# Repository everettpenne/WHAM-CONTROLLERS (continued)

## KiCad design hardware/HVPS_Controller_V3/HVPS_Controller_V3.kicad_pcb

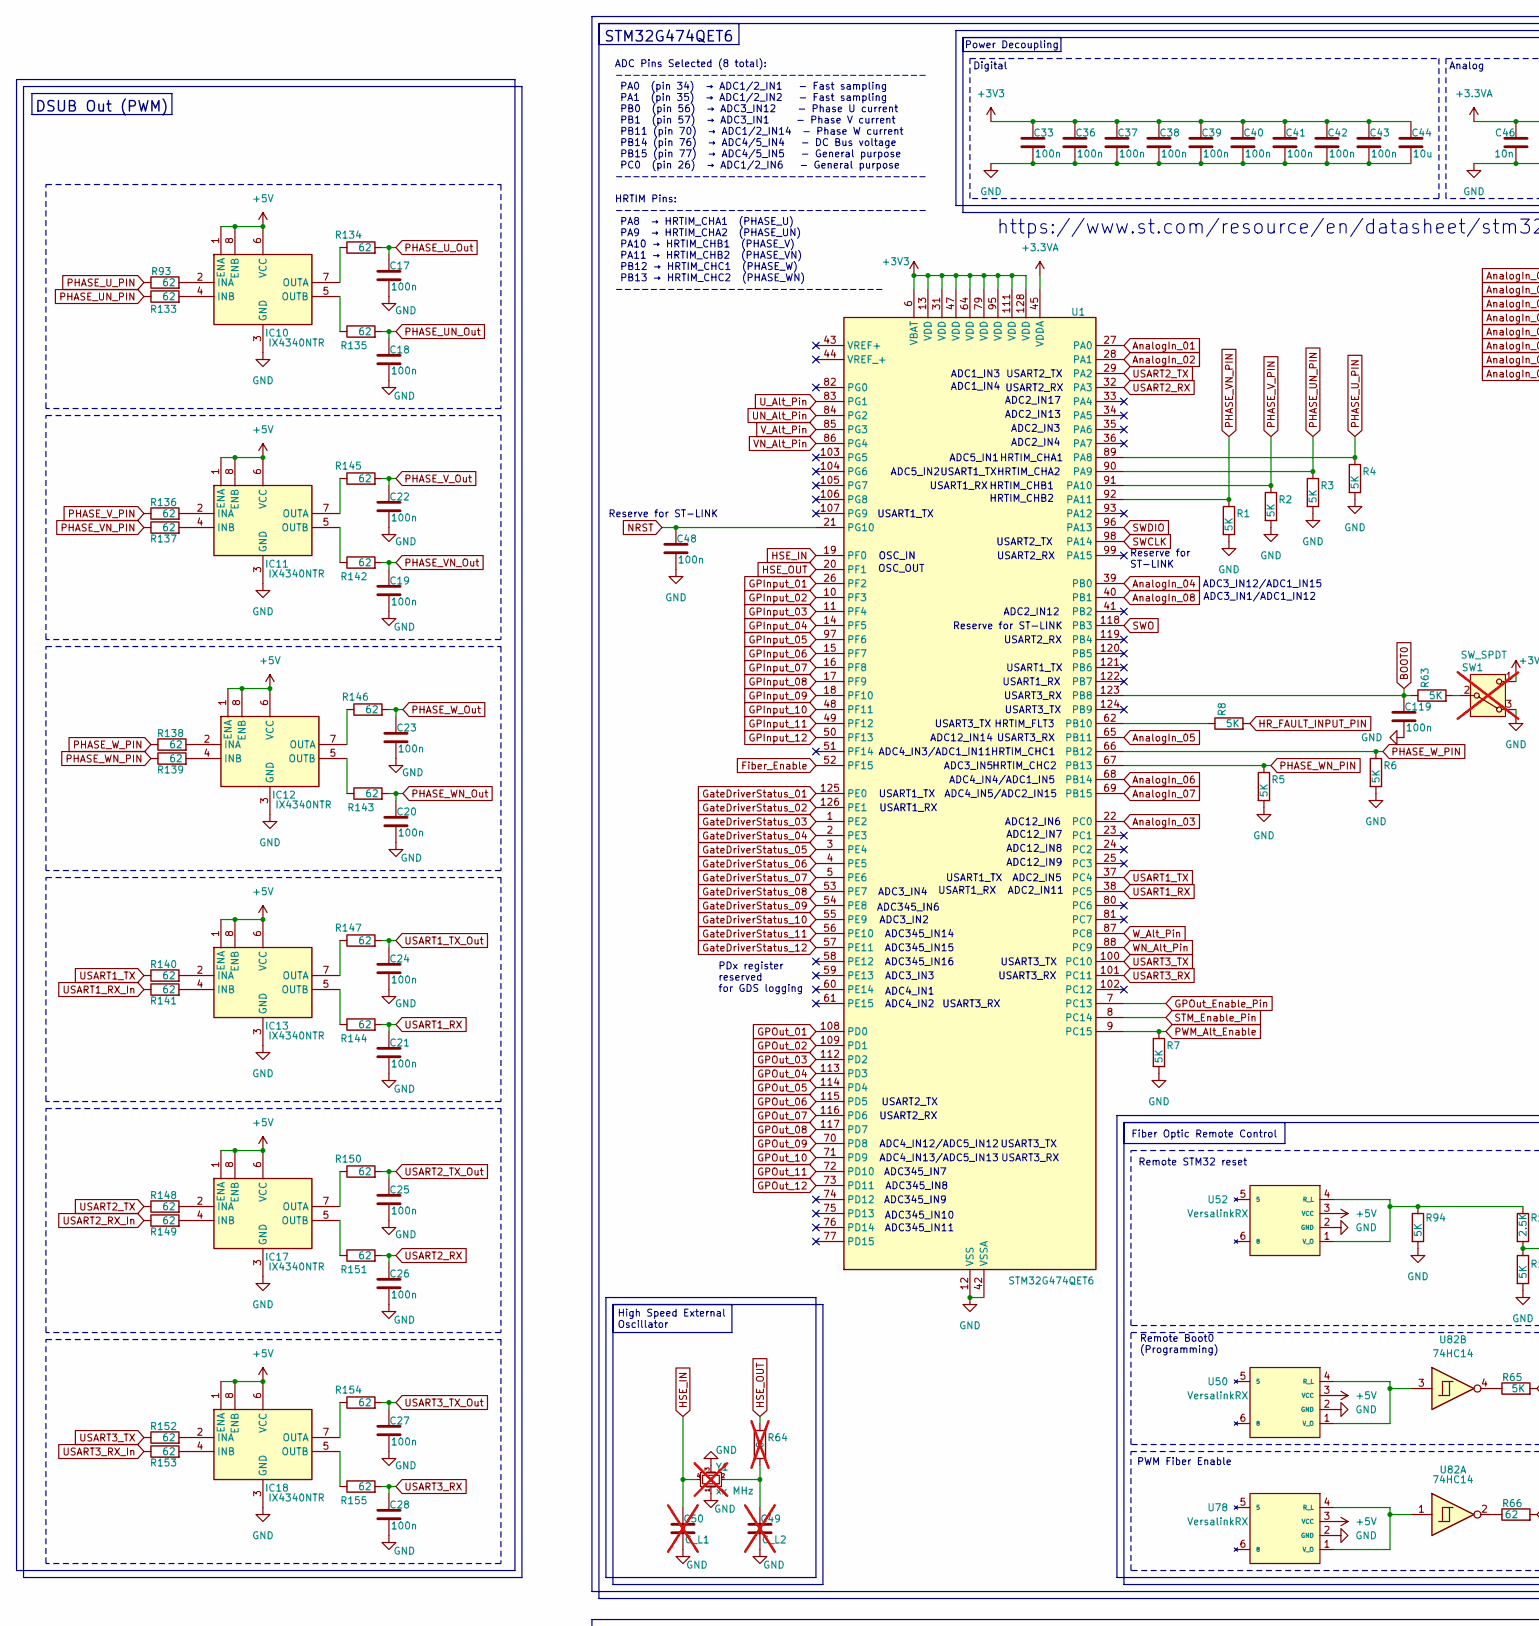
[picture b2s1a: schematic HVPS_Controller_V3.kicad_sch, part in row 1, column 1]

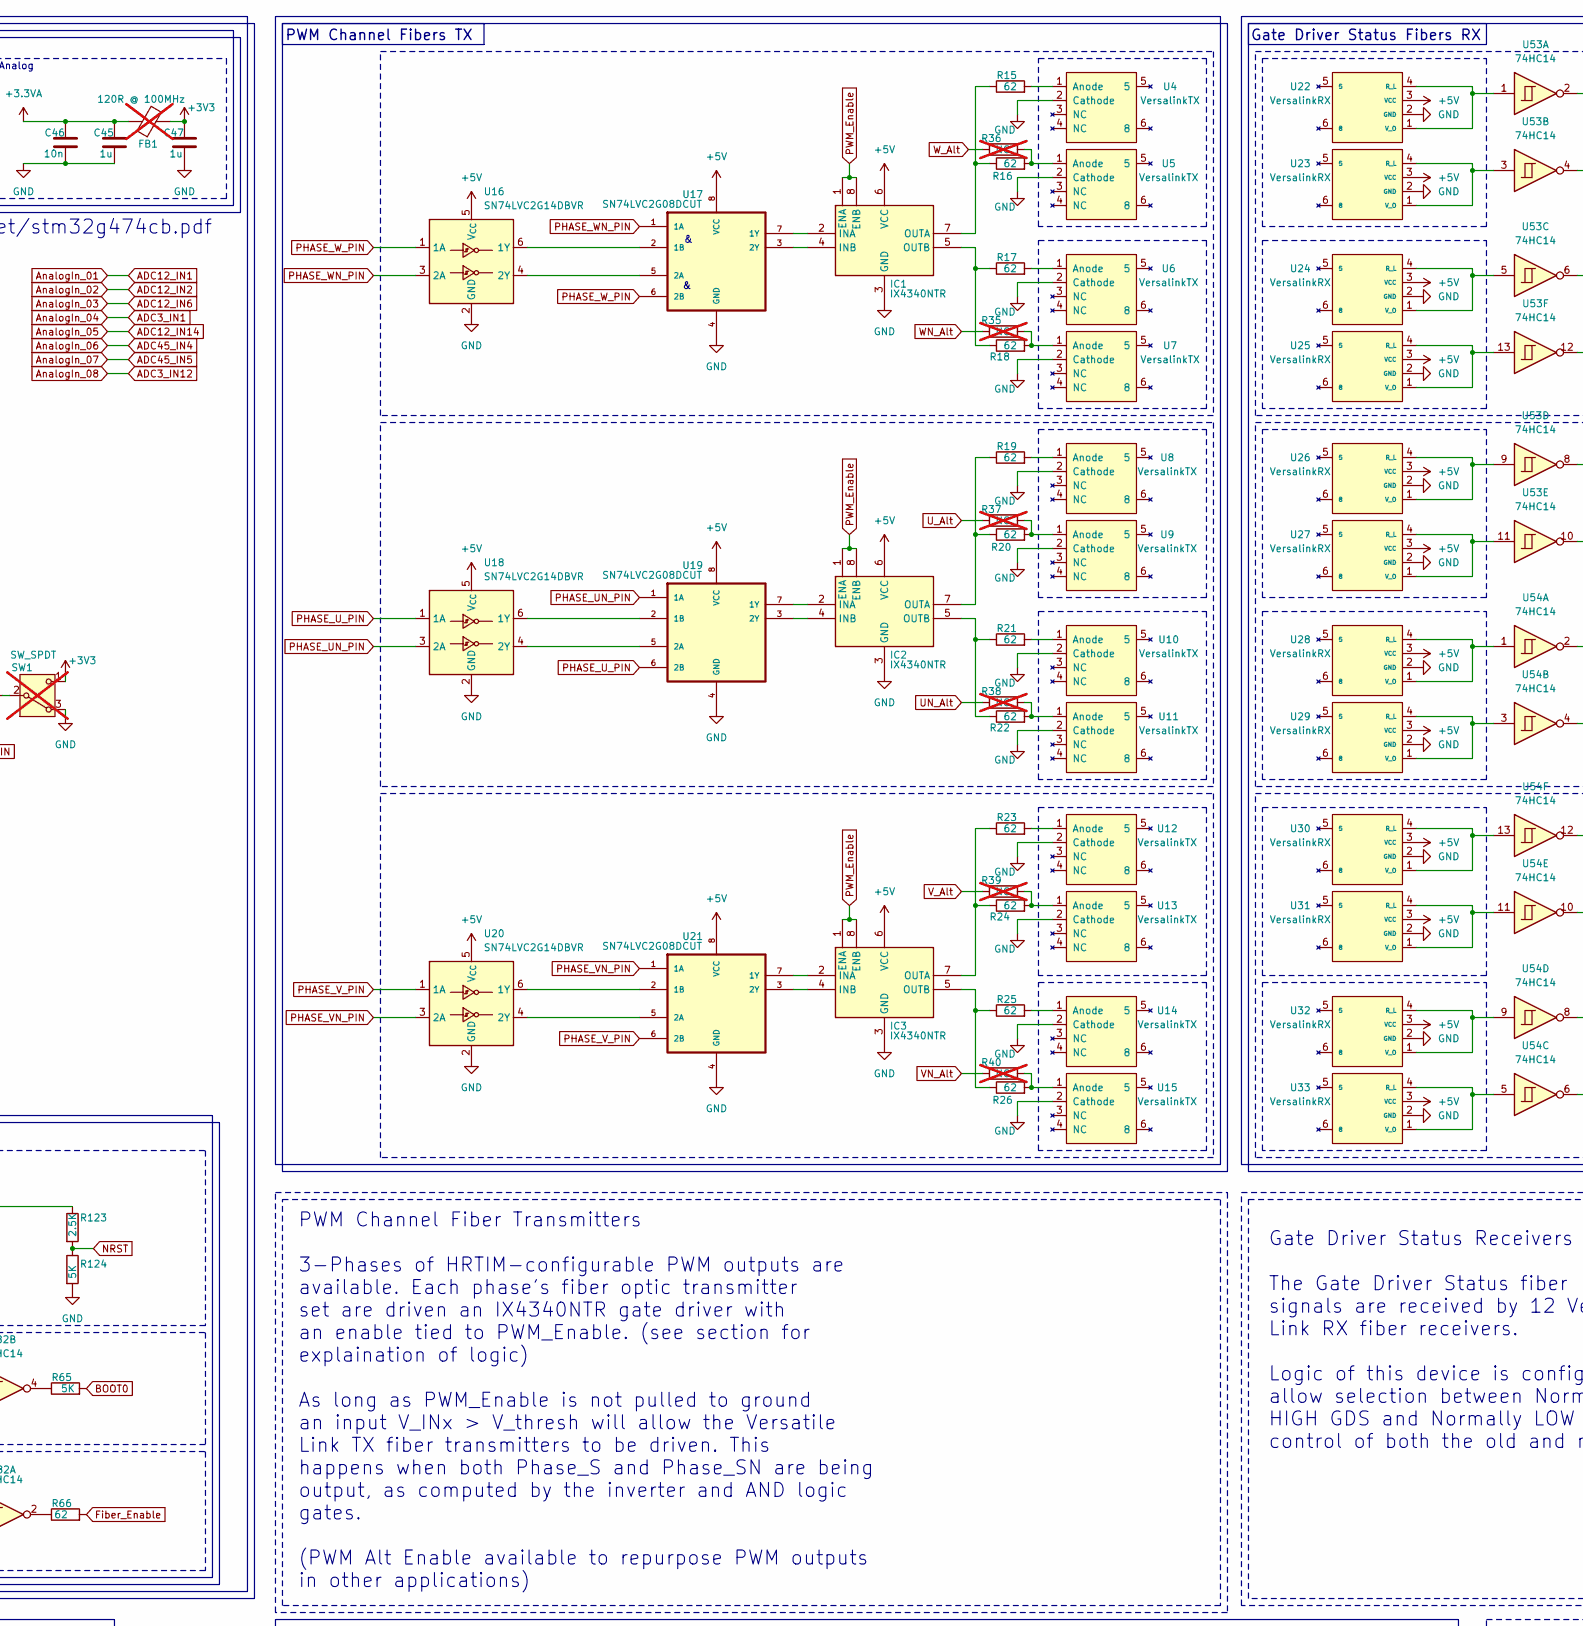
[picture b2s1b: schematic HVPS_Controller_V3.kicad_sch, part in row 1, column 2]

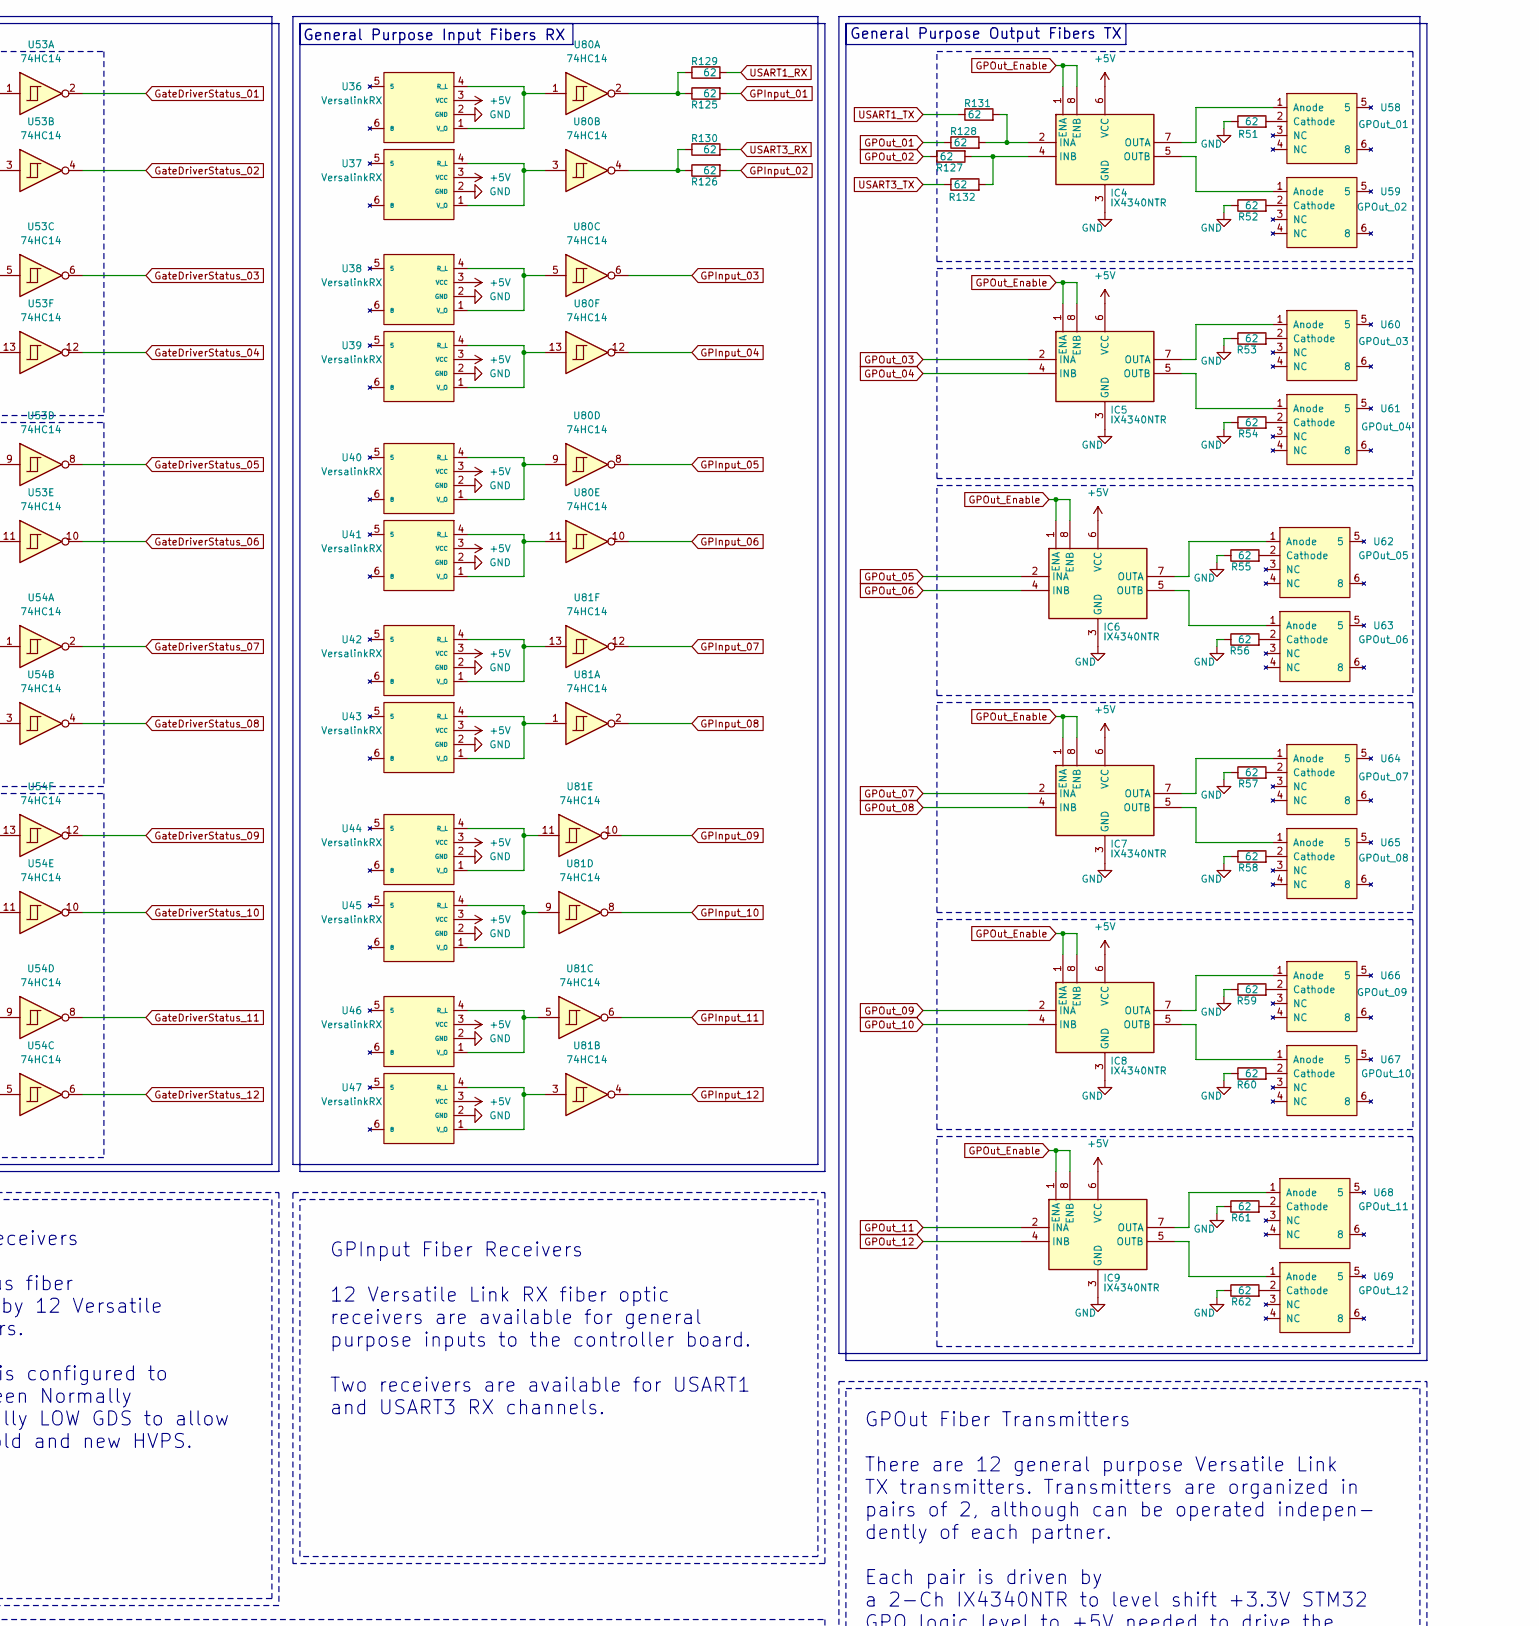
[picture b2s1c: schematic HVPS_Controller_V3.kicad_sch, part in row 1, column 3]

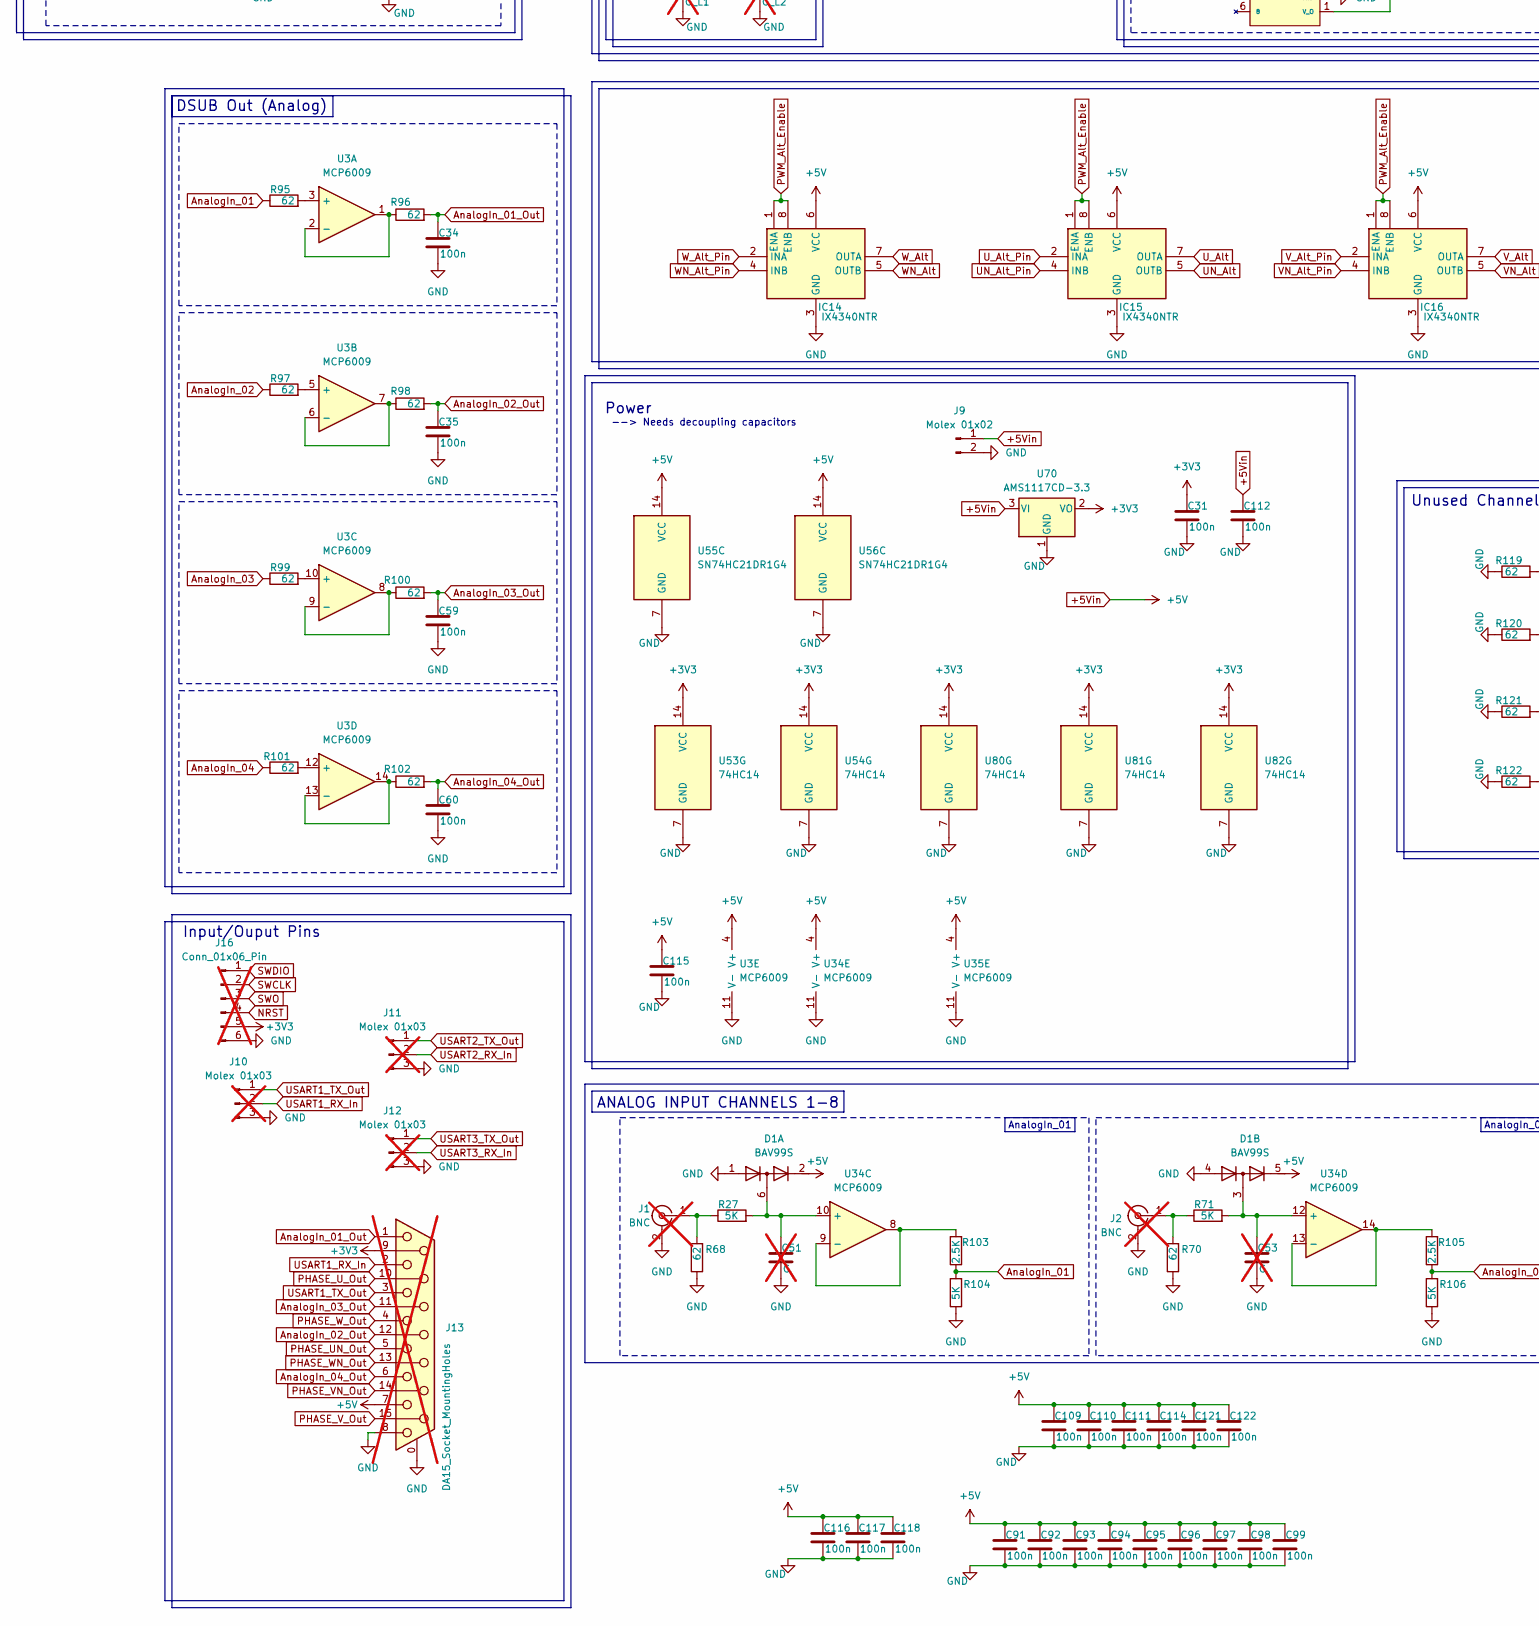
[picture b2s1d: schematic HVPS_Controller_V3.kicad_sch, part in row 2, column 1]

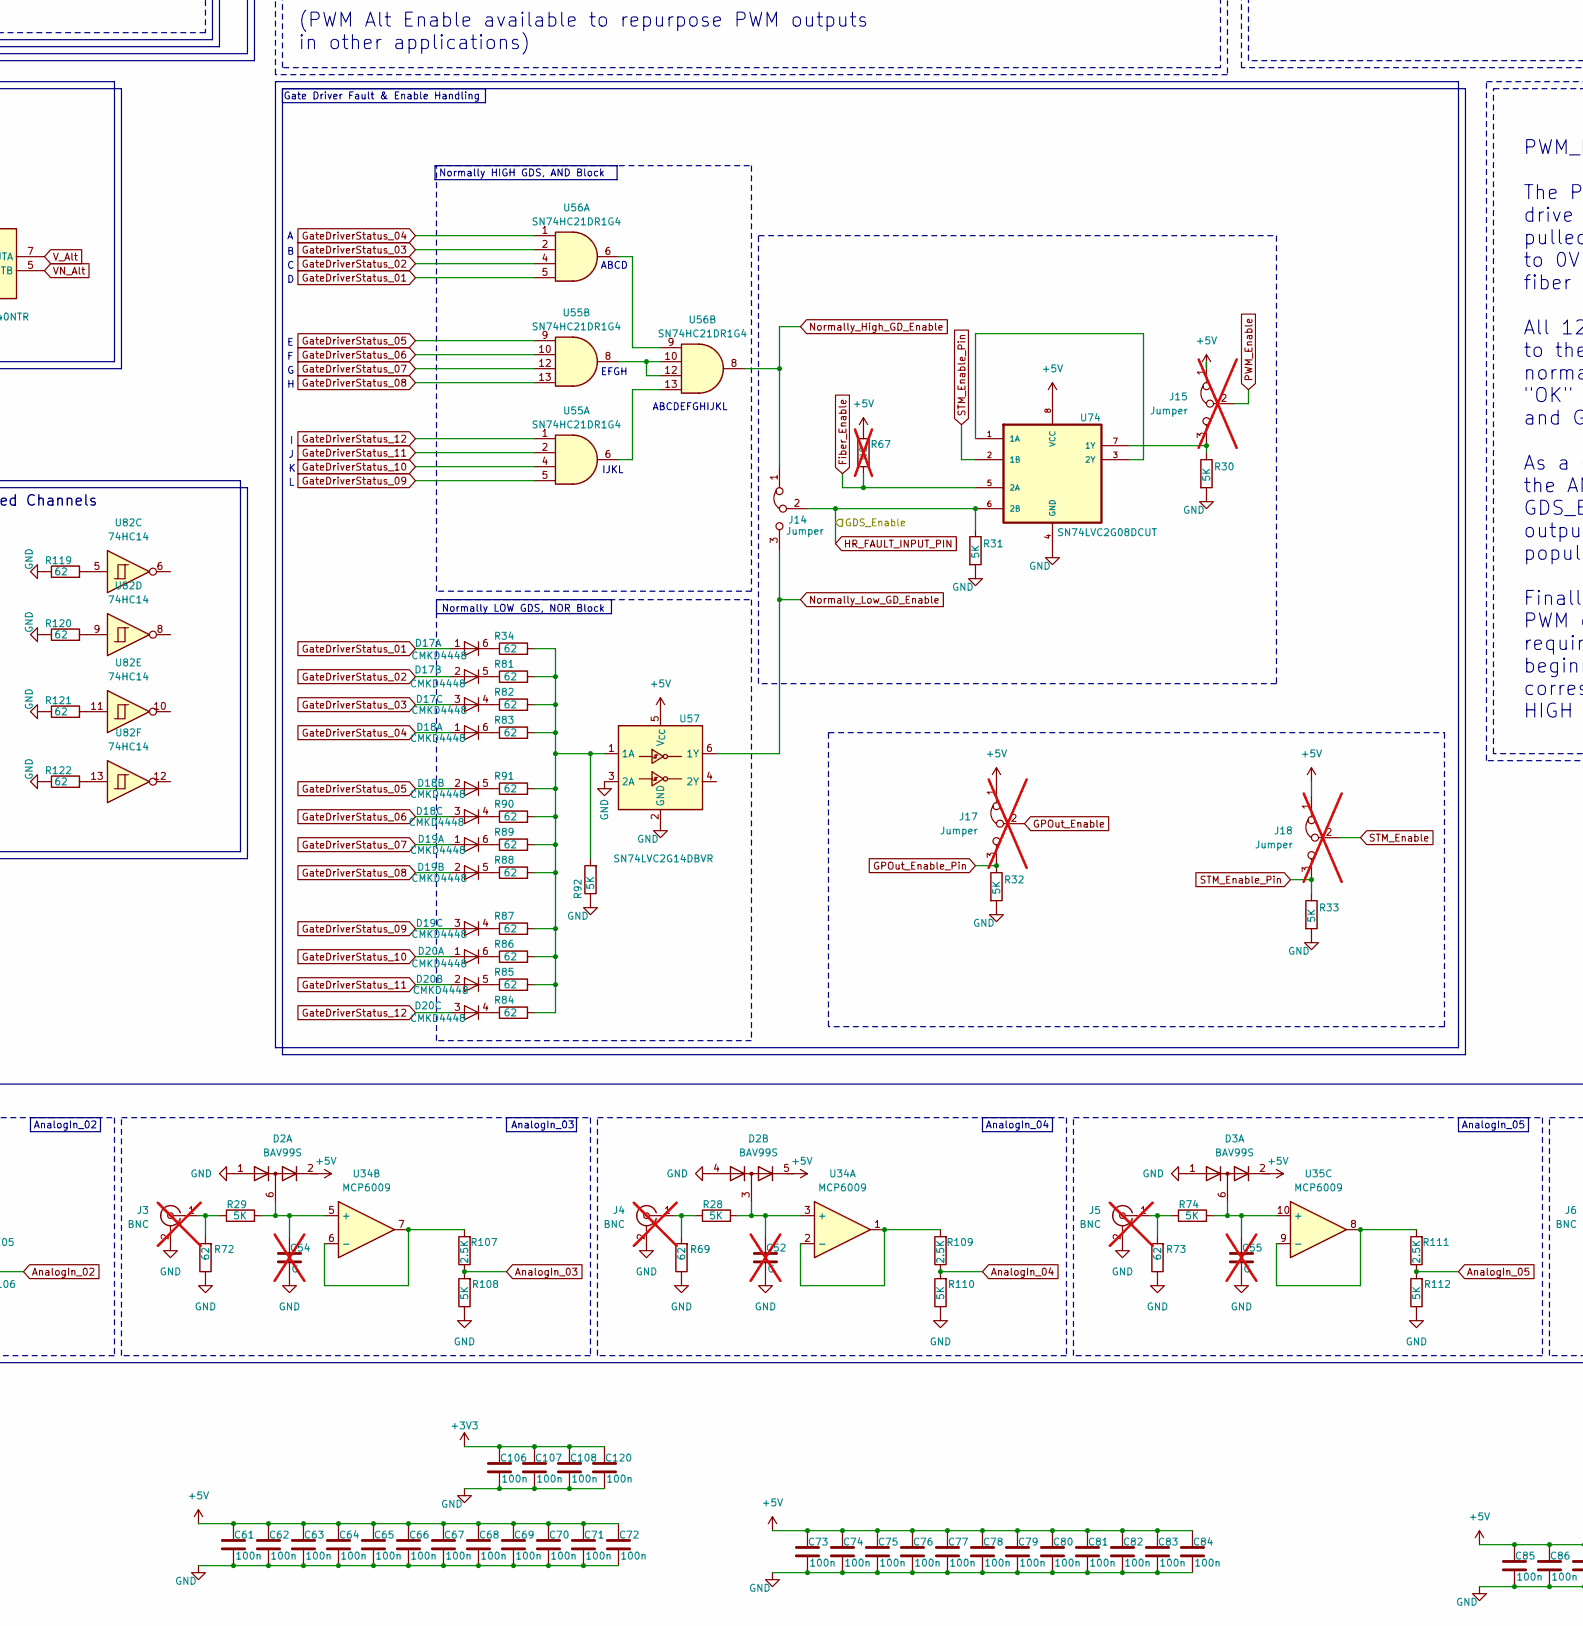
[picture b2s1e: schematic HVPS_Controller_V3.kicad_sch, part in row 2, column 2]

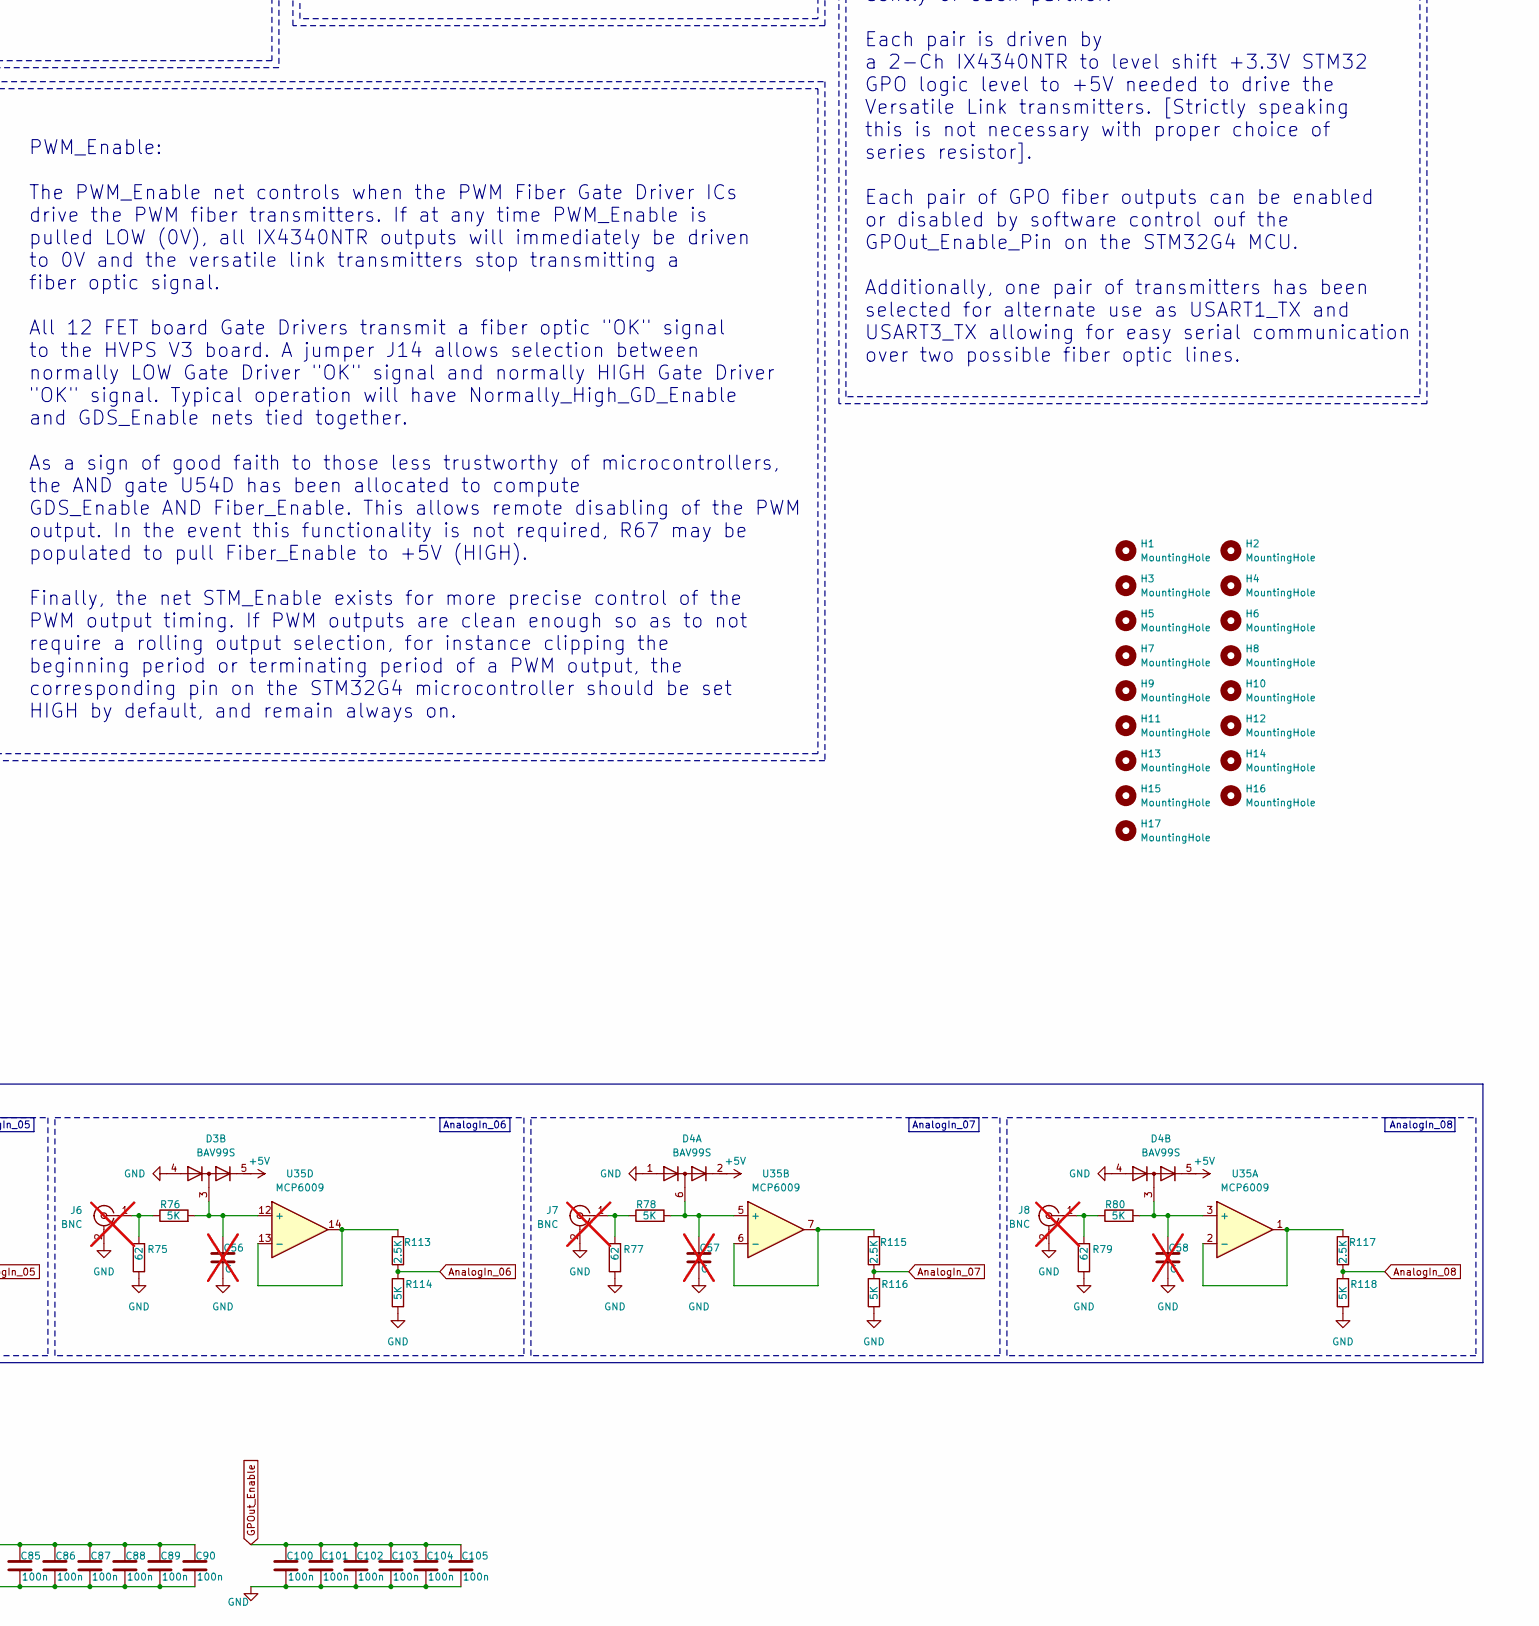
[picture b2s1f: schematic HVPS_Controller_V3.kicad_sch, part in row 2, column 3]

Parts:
C17, C18, C19, C20, C21, C22, C23, C24, C25, C26, C27, C28, C34, C35, C59, C60, C109, C110, C111, C114, C121, C122: 100n; C_1206_3216Metric_Pad1.33x1.80mm_HandSolder
C31, C33, C36, C37, C38, C39, C40, C41, C42, C43, C48, C61, C62, C63, C64, C65, C66, C67, C68, C69, C70, C71, C72, C73, C74, C75, C76, C77, C78, C79, C80, C81, C82, C83, C84, C85, C86, C87, C88, C89, C90, C91, C92, C93, C94, C95, C96, C97, C98, C99, C100, C101, C102, C103, C104, C105, C106, C107, C108, C112, C115, C116, C117, C118, C119, C120: 100n; C_0805_2012Metric_Pad1.18x1.45mm_HandSolder
C44: 10u; C_0805_2012Metric_Pad1.18x1.45mm_HandSolder
C45, C47: 1u; C_0805_2012Metric_Pad1.18x1.45mm_HandSolder
C46: 10n; C_0805_2012Metric_Pad1.18x1.45mm_HandSolder
C49: C_L2; C_0805_2012Metric_Pad1.18x1.45mm_HandSolder; not fitted
C50: C_L1; C_0805_2012Metric_Pad1.18x1.45mm_HandSolder; not fitted
C51, C52, C53, C54, C55, C56, C57, C58: C; C_1206_3216Metric_Pad1.33x1.80mm_HandSolder; not fitted
D1, D2, D3, D4: BAV99S; SOT-363_SC-70-6
D17, D18, D19, D20: CMKD4448; SOT-363_SC-70-6
FB1: 120R @ 100MHz; Ferrite_1206_3216Metric_Pad1.42x1.75mm_BigPads; not fitted
H1, H2, H3, H4, H5, H6, H7, H8, H9, H10, H11, H12, H13, H14, H15, H16, H17: MountingHole; MountingHole_2mm
IC1, IC2, IC3, IC4, IC5, IC6, IC7, IC8, IC9, IC10, IC11, IC12, IC13, IC14, IC15, IC16, IC17, IC18: IX4340NTR; SOIC-8_5.3x5.3mm_P1.27mm; Mouser Part Number 747-IX4340NTR
J1, J2, J3, J4, J5, J6, J7, J8: BNC; BNC_TEConnectivity_1478204_Vertical; not fitted
J9: Molex 01x02; Molex_KK-396_5273-02A_1x02_P3.96mm_Vertical
J10, J11, J12: Molex 01x03; Molex_KK-254_AE-6410-03A_1x03_P2.54mm_Vertical; not fitted
J13: DA15_Socket_MountingHoles; DSUB-15-HD_Pins_Vertical_P2.29x1.98mm_MountingHoles; not fitted
J14: Jumper; PinHeader_1x03_P2.54mm_Vertical
J15, J17, J18: Jumper; PinHeader_1x03_P2.54mm_Vertical; not fitted
J16: Conn_01x06_Pin; Molex_KK-254_AE-6410-06A_1x06_P2.54mm_Vertical; not fitted
R1, R2, R3, R4, R5, R6, R7, R8, R30, R31, R32, R33, R63, R65, R92, R94, R124: 5K; R_0805_2012Metric_Pad1.20x1.40mm_HandSolder
R15, R16, R17, R18, R19, R20, R21, R22, R23, R24, R25, R26, R51, R52, R53, R54, R55, R56, R57, R58, R59, R60, R61, R62, R68, R69, R70, R72, R73, R75, R77, R79, R93, R95, R96, R97, R98, R99, R100, R101, R102, R133, R134, R135, R136, R137, R138, R139, R140, R141, R142, R143, R144, R145, R146, R147, R148, R149, R150, R151, R152, R153, R154, R155: 62; R_1206_3216Metric_Pad1.30x1.75mm_HandSolder
R27, R28, R29, R71, R74, R76, R78, R80, R104, R106, R108, R110, R112, R114, R116, R118: 5K; R_1206_3216Metric_Pad1.30x1.75mm_HandSolder
R34, R66, R81, R82, R83, R84, R85, R86, R87, R88, R89, R90, R91, R119, R120, R121, R122, R125, R126, R127, R128, R129, R130, R131, R132: 62; R_0805_2012Metric_Pad1.20x1.40mm_HandSolder
R35, R36, R37, R38, R39, R40: NC; R_1206_3216Metric_Pad1.30x1.75mm_HandSolder; not fitted
R64: 0; R_0805_2012Metric_Pad1.20x1.40mm_HandSolder; not fitted
R67: NC; R_0805_2012Metric_Pad1.20x1.40mm_HandSolder; not fitted
R103, R105, R107, R109, R111, R113, R115, R117: 2.5K; R_1206_3216Metric_Pad1.30x1.75mm_HandSolder
R123: 2.5K; R_0805_2012Metric_Pad1.20x1.40mm_HandSolder
SW1: SW_SPDT; Molex_KK-254_AE-6410-03A_1x03_P2.54mm_Vertical; not fitted
U1: STM32G474QET6; LQFP-128_14x14mm_P0.4mm
U3, U34, U35: MCP6009; TSSOP-14_4.4x5mm_P0.65mm
U4, U5, U6, U7, U8, U9, U10, U11, U12, U13, U14, U15: VersalinkTX; Versalink-Vertical
U16, U18, U20, U57: SN74LVC2G14DBVR; SOT-23-6
U17, U19, U21, U74: SN74LVC2G08DCUT; SOP50P310X90-8N
U22, U23, U24, U25, U26, U27, U28, U29, U30, U31, U32, U33, U36, U37, U38, U39, U40, U41, U42, U43, U44, U45, U46, U47, U50, U52, U78: VersalinkRX; Versalink-Vertical
U53, U54, U80, U81, U82: 74HC14; SOIC-14_3.9x8.7mm_P1.27mm
U55, U56: SN74HC21DR1G4; SOIC-14_3.9x8.7mm_P1.27mm
U58: GPOut_01; Versalink-Vertical
U59: GPOut_02; Versalink-Vertical
U60: GPOut_03; Versalink-Vertical
U61: GPOut_04; Versalink-Vertical
U62: GPOut_05; Versalink-Vertical
U63: GPOut_06; Versalink-Vertical
U64: GPOut_07; Versalink-Vertical
U65: GPOut_08; Versalink-Vertical
U66: GPOut_09; Versalink-Vertical
U67: GPOut_10; Versalink-Vertical
U68: GPOut_11; Versalink-Vertical
U69: GPOut_12; Versalink-Vertical
U70: AMS1117CD-3.3; TO-252-3_TabPin2
Y1: xx MHz; Crystal_SMD_3225-4Pin_3.2x2.5mm_HandSoldering; not fitted

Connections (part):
+3.3VA: C45.1, C46.1, FB1.1, U1.45 (VDDA)
+3V3: C31.1, C33.1, C36.1, C37.1, C38.1, C39.1, C40.1, C41.1, C42.1, C43.1, C44.1, C47.1, C106.1, C107.1, C108.1, C120.1, FB1.2, J13.9, J16.5, SW1.1 (C), U1.6 (VBAT), U1.13 (VDD), U1.31 (VDD), U1.47 (VDD), U1.64 (VDD), U1.79 (VDD), U1.95 (VDD), U1.111 (VDD), U1.128 (VDD), U53.14 (VCC), U54.14 (VCC), U70.2 (VO), U80.14 (VCC), U81.14 (VCC), U82.14 (VCC)
+5Vin: C61.1, C62.1, C63.1, C64.1, C65.1, C66.1, C67.1, C68.1, C69.1, C70.1, C71.1, C72.1, C73.1, C74.1, C75.1, C76.1, C77.1, C78.1, C79.1, C80.1, C81.1, C82.1, C83.1, C84.1, C85.1, C86.1, C87.1, C88.1, C89.1, C90.1, C91.1, C92.1, C93.1, C94.1, C95.1, C96.1, C97.1, C98.1, C99.1, C109.1, C110.1, C111.1, C112.1, C114.1, C115.1, C116.1, C117.1, C118.1, C121.1, C122.1, D1.2 (K2), D1.5 (K4), D2.2 (K2), D2.5 (K4), D3.2 (K2), D3.5 (K4), D4.2 (K2), D4.5 (K4), IC1.6 (VCC), IC2.6 (VCC), IC3.6 (VCC), IC4.6 (VCC), IC5.6 (VCC), IC6.6 (VCC), IC7.6 (VCC), IC8.6 (VCC), IC9.6 (VCC), IC10.1 (ENA), IC10.6 (VCC), IC10.8 (ENB), IC11.1 (ENA), IC11.6 (VCC), IC11.8 (ENB), IC12.1 (ENA), IC12.6 (VCC), IC12.8 (ENB), IC13.1 (ENA), IC13.6 (VCC), IC13.8 (ENB), IC14.6 (VCC), IC15.6 (VCC)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
ADC3_IN1: R101.1, R109.1, R110.2, U1.39 (PB0)
ADC3_IN12: R117.1, R118.2, U1.40 (PB1)
ADC12_IN1: R95.1, R103.1, R104.2, U1.27 (PA0)
ADC12_IN2: R97.1, R105.1, R106.2, U1.28 (PA1)
ADC12_IN6: R99.1, R107.1, R108.2, U1.22 (PC0)
ADC12_IN14: R111.1, R112.2, U1.65 (PB11)
ADC45_IN4: R113.1, R114.2, U1.68 (PB14)
ADC45_IN5: R115.1, R116.2, U1.69 (PB15)
AnalogIn_01_Out: C34.1, J13.1, R96.2
AnalogIn_02_Out: C35.1, J13.12, R98.2
AnalogIn_03_Out: C59.1, J13.11 (P111), R100.2
AnalogIn_04_Out: C60.1, J13.6, R102.2
BOOT0: C119.1, R63.1, R65.2, U1.123 (PB8)
Fiber_Enable: R66.2, R67.1, U1.52 (PF15), U74.5 (2A)
GND: C17.2, C18.2, C19.2, C20.2, C21.2, C22.2, C23.2, C24.2, C25.2, C26.2, C27.2, C28.2, C31.2, C33.2, C34.2, C35.2, C36.2, C37.2, C38.2, C39.2, C40.2, C41.2, C42.2, C43.2, C44.2, C45.2, C46.2, C47.2, C48.2, C49.2, C50.2, C51.2, C52.2, C53.2, C54.2, C55.2, C56.2, C57.2, C58.2, C59.2, C60.2, C61.2, C62.2, C63.2, C64.2, C65.2, C66.2, C67.2, C68.2, C69.2, C70.2, C71.2, C72.2, C73.2, C74.2, C75.2, C76.2, C77.2, C78.2, C79.2, C80.2, C81.2, C82.2, C83.2, C84.2, C85.2, C86.2, C87.2, C88.2, C89.2, C90.2, C91.2, C92.2, C93.2, C94.2, C95.2, C96.2, C97.2, C98.2, C99.2, C100.2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
GPInput_01: R125.2, U1.26 (PF2)
GPInput_02: R126.2, U1.10 (PF3)
GPInput_03: U1.11 (PF4), U80.6
GPInput_04: U1.14 (PF5), U80.12
GPInput_05: U1.97 (PF6), U80.8
GPInput_06: U1.15 (PF7), U80.10
GPInput_07: U1.16 (PF8), U81.12
GPInput_08: U1.17 (PF9), U81.2
GPInput_09: U1.18 (PF10), U81.10
GPInput_10: U1.48 (PF11), U81.8
GPInput_11: U1.49 (PF12), U81.6
GPInput_12: U1.50 (PF13), U81.4
GPOut_01: R128.1, U1.108 (PD0)
GPOut_02: R127.1, U1.109 (PD1)
GPOut_03: IC5.2 (INA), U1.112 (PD2)
GPOut_04: IC5.4 (INB), U1.113 (PD3)
GPOut_05: IC6.2 (INA), U1.114 (PD4)
GPOut_06: IC6.4 (INB), U1.115 (PD5)
GPOut_07: IC7.2 (INA), U1.116 (PD6)
GPOut_08: IC7.4 (INB), U1.117 (PD7)
GPOut_09: IC8.2 (INA), U1.70 (PD8)
GPOut_10: IC8.4 (INB), U1.71 (PD9)
GPOut_11: IC9.2 (INA), U1.72 (PD10)
GPOut_12: IC9.4 (INB), U1.73 (PD11)
GPOut_Enable: C100.1, C101.1, C102.1, C103.1, C104.1, C105.1, IC4.1 (ENA), IC4.8 (ENB), IC5.1 (ENA), IC5.8 (ENB), IC6.1 (ENA), IC6.8 (ENB), IC7.1 (ENA), IC7.8 (ENB), IC8.1 (ENA), IC8.8 (ENB), IC9.1 (ENA), IC9.8 (ENB), J17.2
GPOut_Enable_Pin: J17.3, R32.1, U1.7 (PC13)
GateDriverStatus_01: D17.1 (A), U1.125 (PE0), U53.2, U56.5
GateDriverStatus_02: D17.2 (A), U1.126 (PE1), U53.4, U56.4
GateDriverStatus_03: D17.3 (A), U1.1 (PE2), U53.6, U56.2
GateDriverStatus_04: D18.1 (A), U1.2 (PE3), U53.12, U56.1
GateDriverStatus_05: D18.2 (A), U1.3 (PE4), U53.8, U55.9
GateDriverStatus_06: D18.3 (A), U1.4 (PE5), U53.10, U55.10
GateDriverStatus_07: D19.1 (A), U1.5 (PE6), U54.2, U55.12
GateDriverStatus_08: D19.2 (A), U1.53 (PE7), U54.4, U55.13
GateDriverStatus_09: D19.3 (A), U1.54 (PE8), U54.12, U55.5
GateDriverStatus_10: D20.1 (A), U1.55 (PE9), U54.10, U55.4
GateDriverStatus_11: D20.2 (A), U1.56 (PE10), U54.8, U55.2
GateDriverStatus_12: D20.3 (A), U1.57 (PE11), U54.6, U55.1
HR_FAULT_INPUT_PIN: J14.2, R8.2, R31.1, U74.6 (2B)
HSE_IN: C50.1, U1.19 (PF0), Y1.4
HSE_OUT: R64.1, U1.20 (PF1)
NRST: C48.1, J16.4, R123.2, R124.1, U1.21 (PG10)
unnamed: C49.1, R64.2, Y1.2
unnamed: C51.1, D1.6 (K3A4), R27.2, U34.10 (+)
unnamed: C53.1, D1.3 (K1A2), R71.2, U34.12 (+)
unnamed: C54.1, D2.6 (K3A4), R29.2, U34.5 (+)
unnamed: C52.1, D2.3 (K1A2), R28.2, U34.3 (+)
unnamed: C55.1, D3.6 (K3A4), R74.2, U35.10 (+)
unnamed: C56.1, D3.3 (K1A2), R76.2, U35.12 (+)
unnamed: C57.1, D4.6 (K3A4), R78.2, U35.5 (+)
unnamed: C58.1, D4.3 (K1A2), R80.2, U35.3 (+)
unnamed: D17.6 (K), R34.1
unnamed: D17.5 (K), R81.1
unnamed: D17.4 (K), R82.1
unnamed: D18.6 (K), R83.1
unnamed: D18.5 (K), R91.1
unnamed: D18.4 (K), R90.1
unnamed: D19.6 (K), R89.1
unnamed: D19.5 (K), R88.1
unnamed: D19.4 (K), R87.1
unnamed: D20.6 (K), R86.1
unnamed: D20.5 (K), R85.1
unnamed: D20.4 (K), R84.1
unnamed: IC1.2 (INA), U17.7 (1Y)
unnamed: IC1.4 (INB), U17.3 (2Y)
unnamed: IC1.7 (OUTA), R15.1, R16.1
unnamed: IC1.5 (OUTB), R17.1, R18.1
unnamed: IC2.2 (INA), U19.7 (1Y)
unnamed: IC2.4 (INB), U19.3 (2Y)
unnamed: IC2.7 (OUTA), R19.1, R20.1
unnamed: IC2.5 (OUTB), R21.1, R22.1
unnamed: IC3.2 (INA), U21.7 (1Y)
unnamed: IC3.4 (INB), U21.3 (2Y)
unnamed: IC3.7 (OUTA), R23.1, R24.1
unnamed: IC3.5 (OUTB), R25.1, R26.1
unnamed: IC4.2 (INA), R128.2, R131.2
unnamed: IC4.4 (INB), R127.2, R132.2
unnamed: IC4.7 (OUTA), U58.1 (Anode)
unnamed: IC4.5 (OUTB), U59.1 (Anode)
unnamed: IC5.7 (OUTA), U60.1 (Anode)
unnamed: IC5.5 (OUTB), U61.1 (Anode)
unnamed: IC6.7 (OUTA), U62.1 (Anode)
unnamed: IC6.5 (OUTB), U63.1 (Anode)
unnamed: IC7.7 (OUTA), U64.1 (Anode)
unnamed: IC7.5 (OUTB), U65.1 (Anode)
unnamed: IC8.7 (OUTA), U66.1 (Anode)
unnamed: IC8.5 (OUTB), U67.1 (Anode)
unnamed: IC9.7 (OUTA), U68.1 (Anode)
unnamed: IC9.5 (OUTB), U69.1 (Anode)
unnamed: IC10.2 (INA), R93.2
unnamed: IC10.4 (INB), R133.2
unnamed: IC10.7 (OUTA), R134.1
unnamed: IC10.5 (OUTB), R135.1
unnamed: IC11.2 (INA), R136.2
unnamed: IC11.4 (INB), R137.2
unnamed: IC11.7 (OUTA), R145.1
unnamed: IC11.5 (OUTB), R142.1
unnamed: IC12.2 (INA), R138.2
unnamed: IC12.4 (INB), R139.2
unnamed: IC12.7 (OUTA), R146.1
unnamed: IC12.5 (OUTB), R143.1
unnamed: IC13.2 (INA), R140.2
unnamed: IC13.4 (INB), R141.2
unnamed: IC13.7 (OUTA), R147.1
unnamed: IC13.5 (OUTB), R144.1
unnamed: IC17.2 (INA), R148.2
unnamed: IC17.4 (INB), R149.2
unnamed: IC17.7 (OUTA), R150.1
unnamed: IC17.5 (OUTB), R151.1
unnamed: IC18.2 (INA), R152.2
unnamed: IC18.4 (INB), R153.2
unnamed: IC18.7 (OUTA), R154.1
unnamed: IC18.5 (OUTB), R155.1
unnamed: J1.1 (In), R27.1, R68.2
unnamed: J2.1 (In), R70.2, R71.1
unnamed: J3.1 (In), R29.1, R72.2
unnamed: J4.1 (In), R28.1, R69.2
unnamed: J5.1 (In), R73.2, R74.1
unnamed: J6.1 (In), R75.2, R76.1
unnamed: J7.1 (In), R77.2, R78.1
unnamed: J8.1 (In), R79.2, R80.1
unnamed: J15.3, R30.1, U74.7 (1Y)
unnamed: R65.1, U82.4
unnamed: R66.1, U82.2
unnamed: R119.2, U82.5
unnamed: R120.2, U82.9
unnamed: R121.2, U82.11
unnamed: R122.2, U82.13
unnamed: R125.1, R129.1, U80.2
unnamed: R126.1, R130.1, U80.4
unnamed: R63.2, SW1.2 (B)
unnamed: R8.1, U1.62 (PB10)
unnamed: R95.2, U3.3 (+)
unnamed: R96.1, U3.1, U3.2 (-)
unnamed: R97.2, U3.5 (+)
unnamed: R98.1, U3.6 (-), U3.7
unnamed: R99.2, U3.10 (+)
unnamed: R100.1, U3.8, U3.9 (-)
unnamed: R101.2, U3.12 (+)
unnamed: R102.1, U3.13 (-), U3.14
unnamed: R15.2, U4.1 (Anode)
unnamed: R16.2, R36.2, U5.1 (Anode)
unnamed: R17.2, U6.1 (Anode)
unnamed: R18.2, R35.2, U7.1 (Anode)
unnamed: R19.2, U8.1 (Anode)
unnamed: R20.2, R37.2, U9.1 (Anode)
unnamed: R21.2, U10.1 (Anode)
unnamed: R22.2, R38.2, U11.1 (Anode)
unnamed: R23.2, U12.1 (Anode)
unnamed: R24.2, R39.2, U13.1 (Anode)
unnamed: R25.2, U14.1 (Anode)
unnamed: R26.2, R40.2, U15.1 (Anode)
unnamed: U16.6 (1Y), U17.2 (1B)
unnamed: U16.4 (2Y), U17.5 (2A)
unnamed: U18.6 (1Y), U19.2 (1B)
unnamed: U18.4 (2Y), U19.5 (2A)
unnamed: U20.6 (1Y), U21.2 (1B)
unnamed: U20.4 (2Y), U21.5 (2A)
unnamed: U22.1 (V_O), U22.4 (R_L), U53.1
unnamed: U23.1 (V_O), U23.4 (R_L), U53.3
unnamed: U24.1 (V_O), U24.4 (R_L), U53.5
unnamed: U25.1 (V_O), U25.4 (R_L), U53.13
unnamed: U26.1 (V_O), U26.4 (R_L), U53.9
unnamed: U27.1 (V_O), U27.4 (R_L), U53.11
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
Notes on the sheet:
ADC3_IN2
USART3_RX
ADC345_IN14
Remote STM32 reset
ADC345_IN11
PWM_Enable: The PWM_Enable net controls when the PWM Fiber Gate Driver ICs drive the PWM fiber transmitters. If at any time PWM_Enable is pulled LOW (0V), all IX4340NTR outputs will immediately be driven to 0V and the versatile link transmitters stop transmitting a fiber optic signal. All 12 FET bo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
HRTIM_CHA2
HRTIM_CHB1
ADC2_IN11
ADC2_IN12
USART3_TX
ADC2_IN3
USART2_TX
AnalogIn_04
HRTIM_CHA1
PDx register reserved for GDS logging
ADC345_IN15
ADC3_IN5
ADC4_IN13/ADC5_IN13
ADC1_IN4
Gate Driver Status Fibers RX
DSUB Out (PWM)
ADC345_IN16
ABCD
PWM Fiber Enable
ADC12_IN7
ADC4_IN4/ADC1_IN5
Normally HIGH GDS, AND Block
USART1_TX
Normally LOW GDS, NOR Block
ADC4_IN1
Input/Ouput Pins
ADC4_IN2
Gate Driver Fault & Enable Handling
AnalogIn_08
EFGH
ANALOG INPUT CHANNELS 1-8
ADC12_IN6
Reserve for ST-LINK
AnalogIn_03

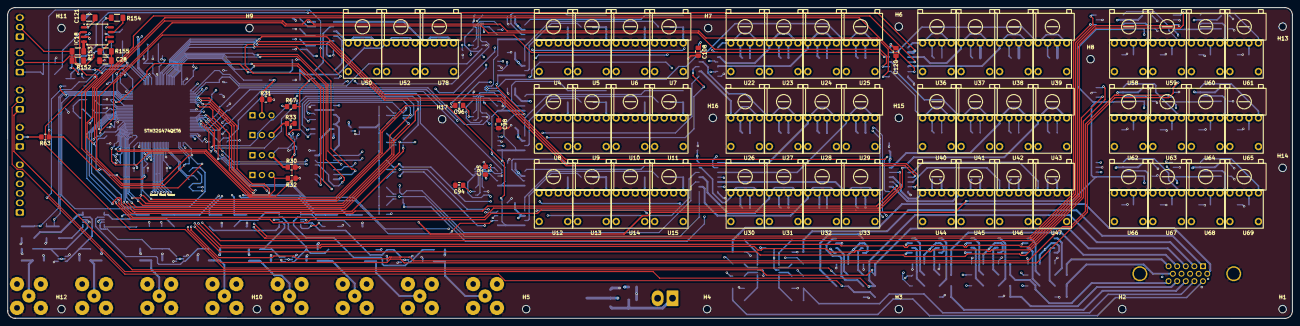
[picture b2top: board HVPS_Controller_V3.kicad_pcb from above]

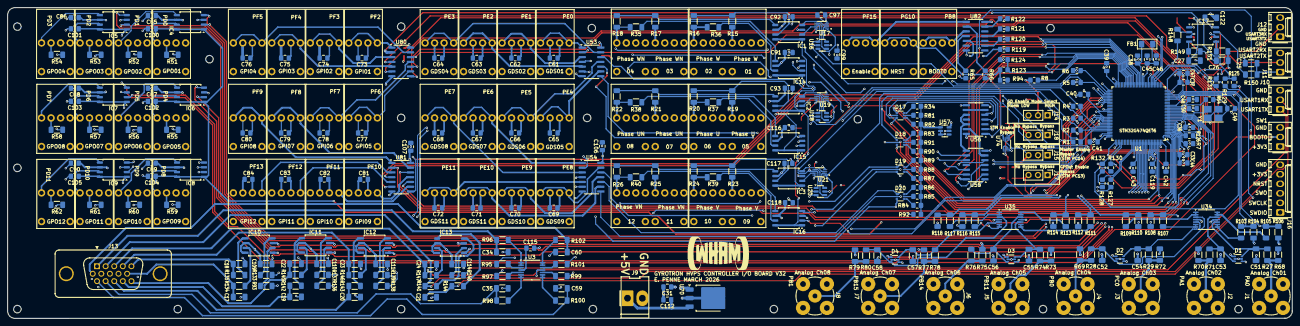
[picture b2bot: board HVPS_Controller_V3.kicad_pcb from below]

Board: 6 copper layers, 342.1 x 82.8 mm, 376 parts (289 on the bottom side), 272 nets.
